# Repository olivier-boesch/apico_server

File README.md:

# apico_server

Code pour ruches connectées

Projet du lycée Saint Exupéry

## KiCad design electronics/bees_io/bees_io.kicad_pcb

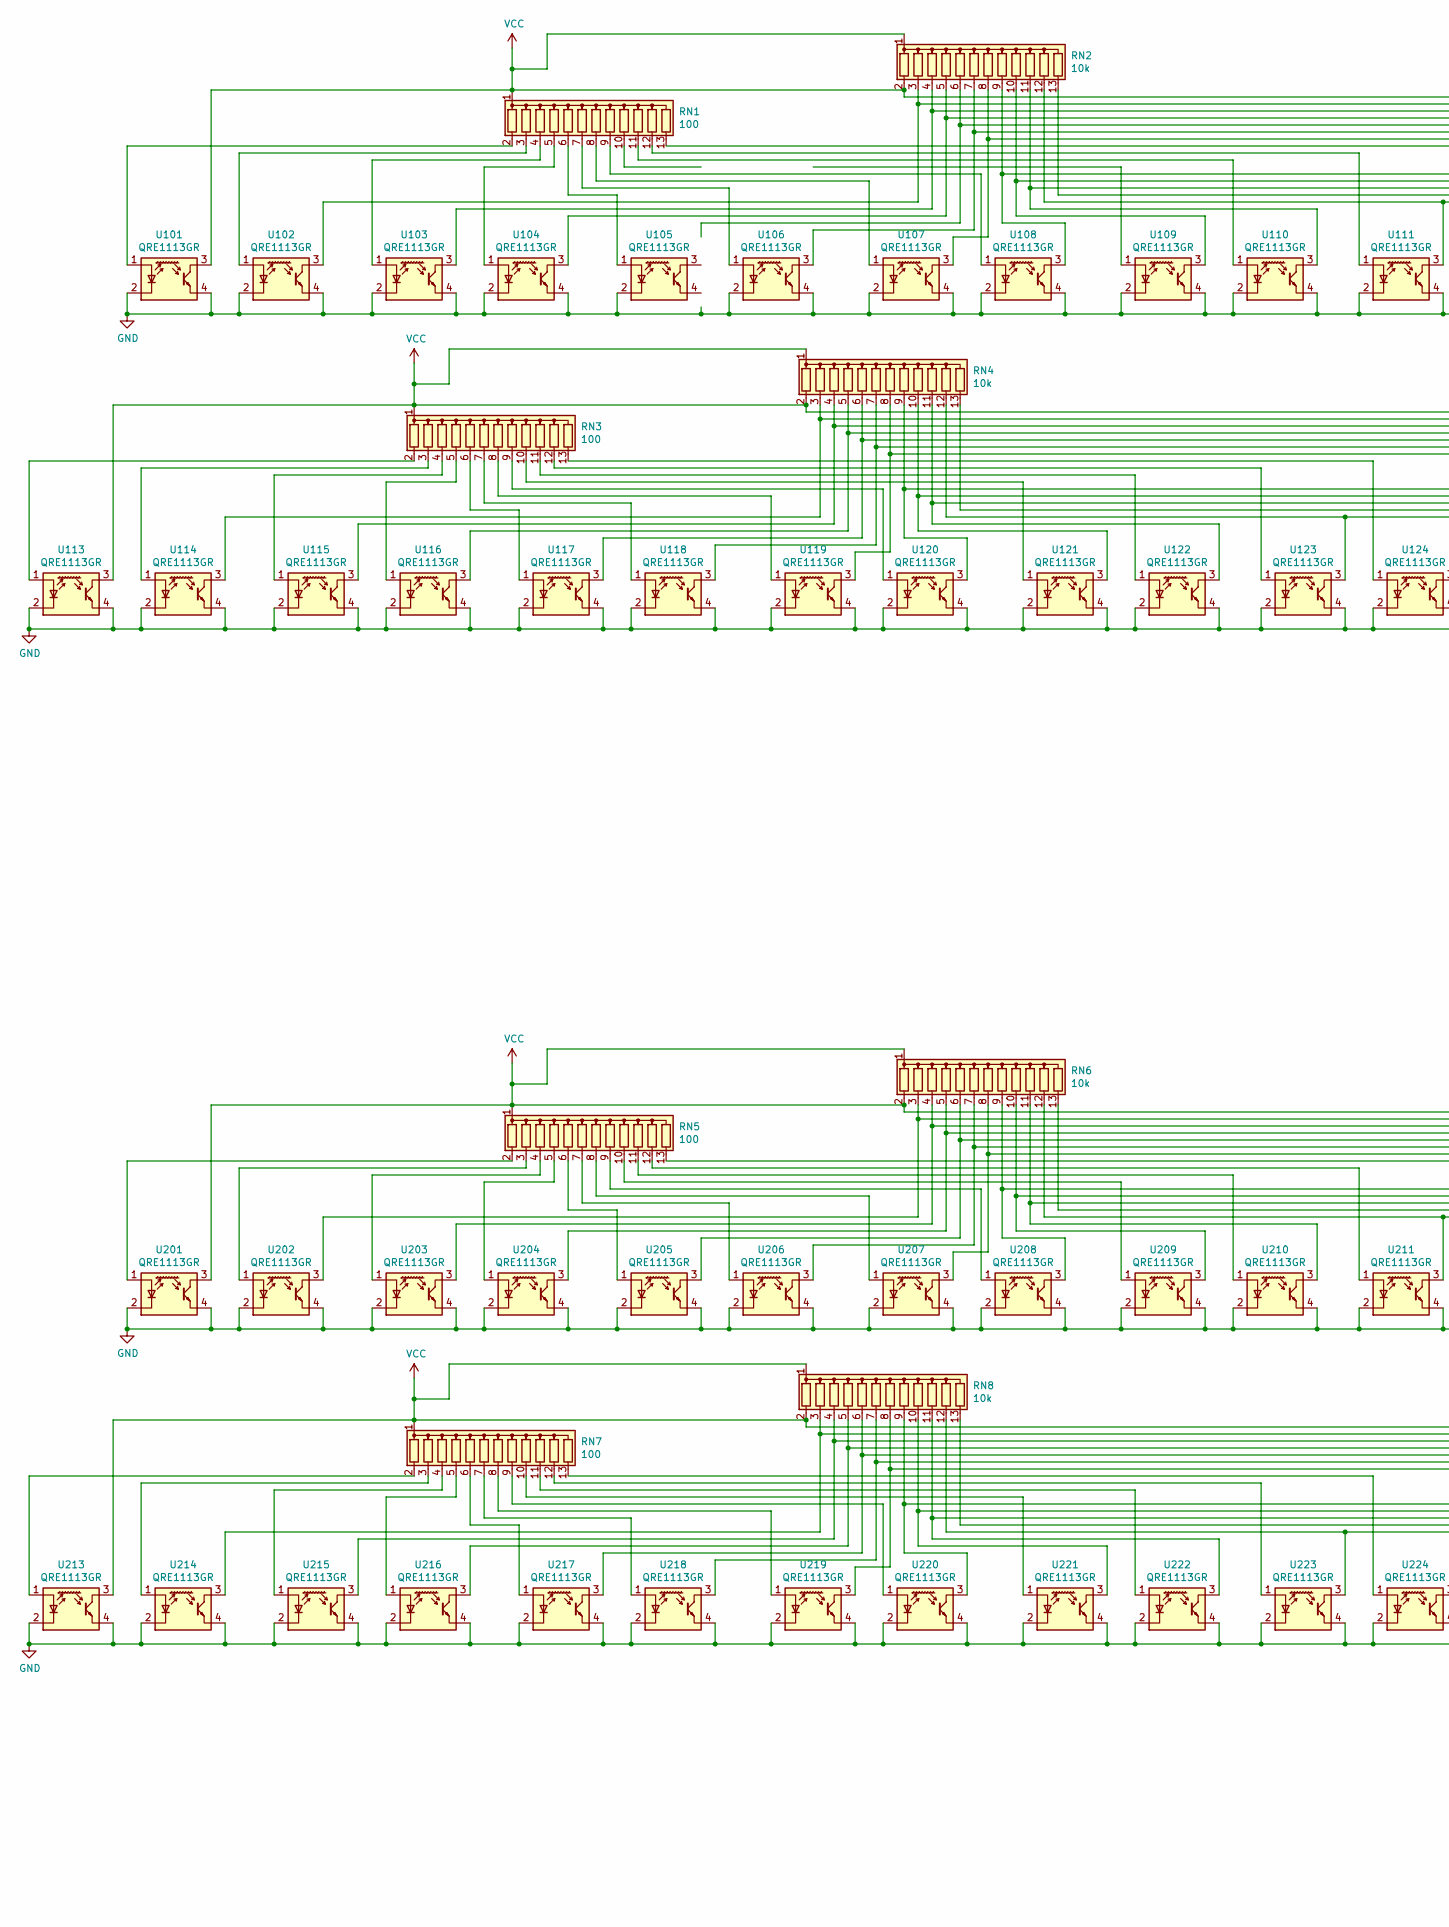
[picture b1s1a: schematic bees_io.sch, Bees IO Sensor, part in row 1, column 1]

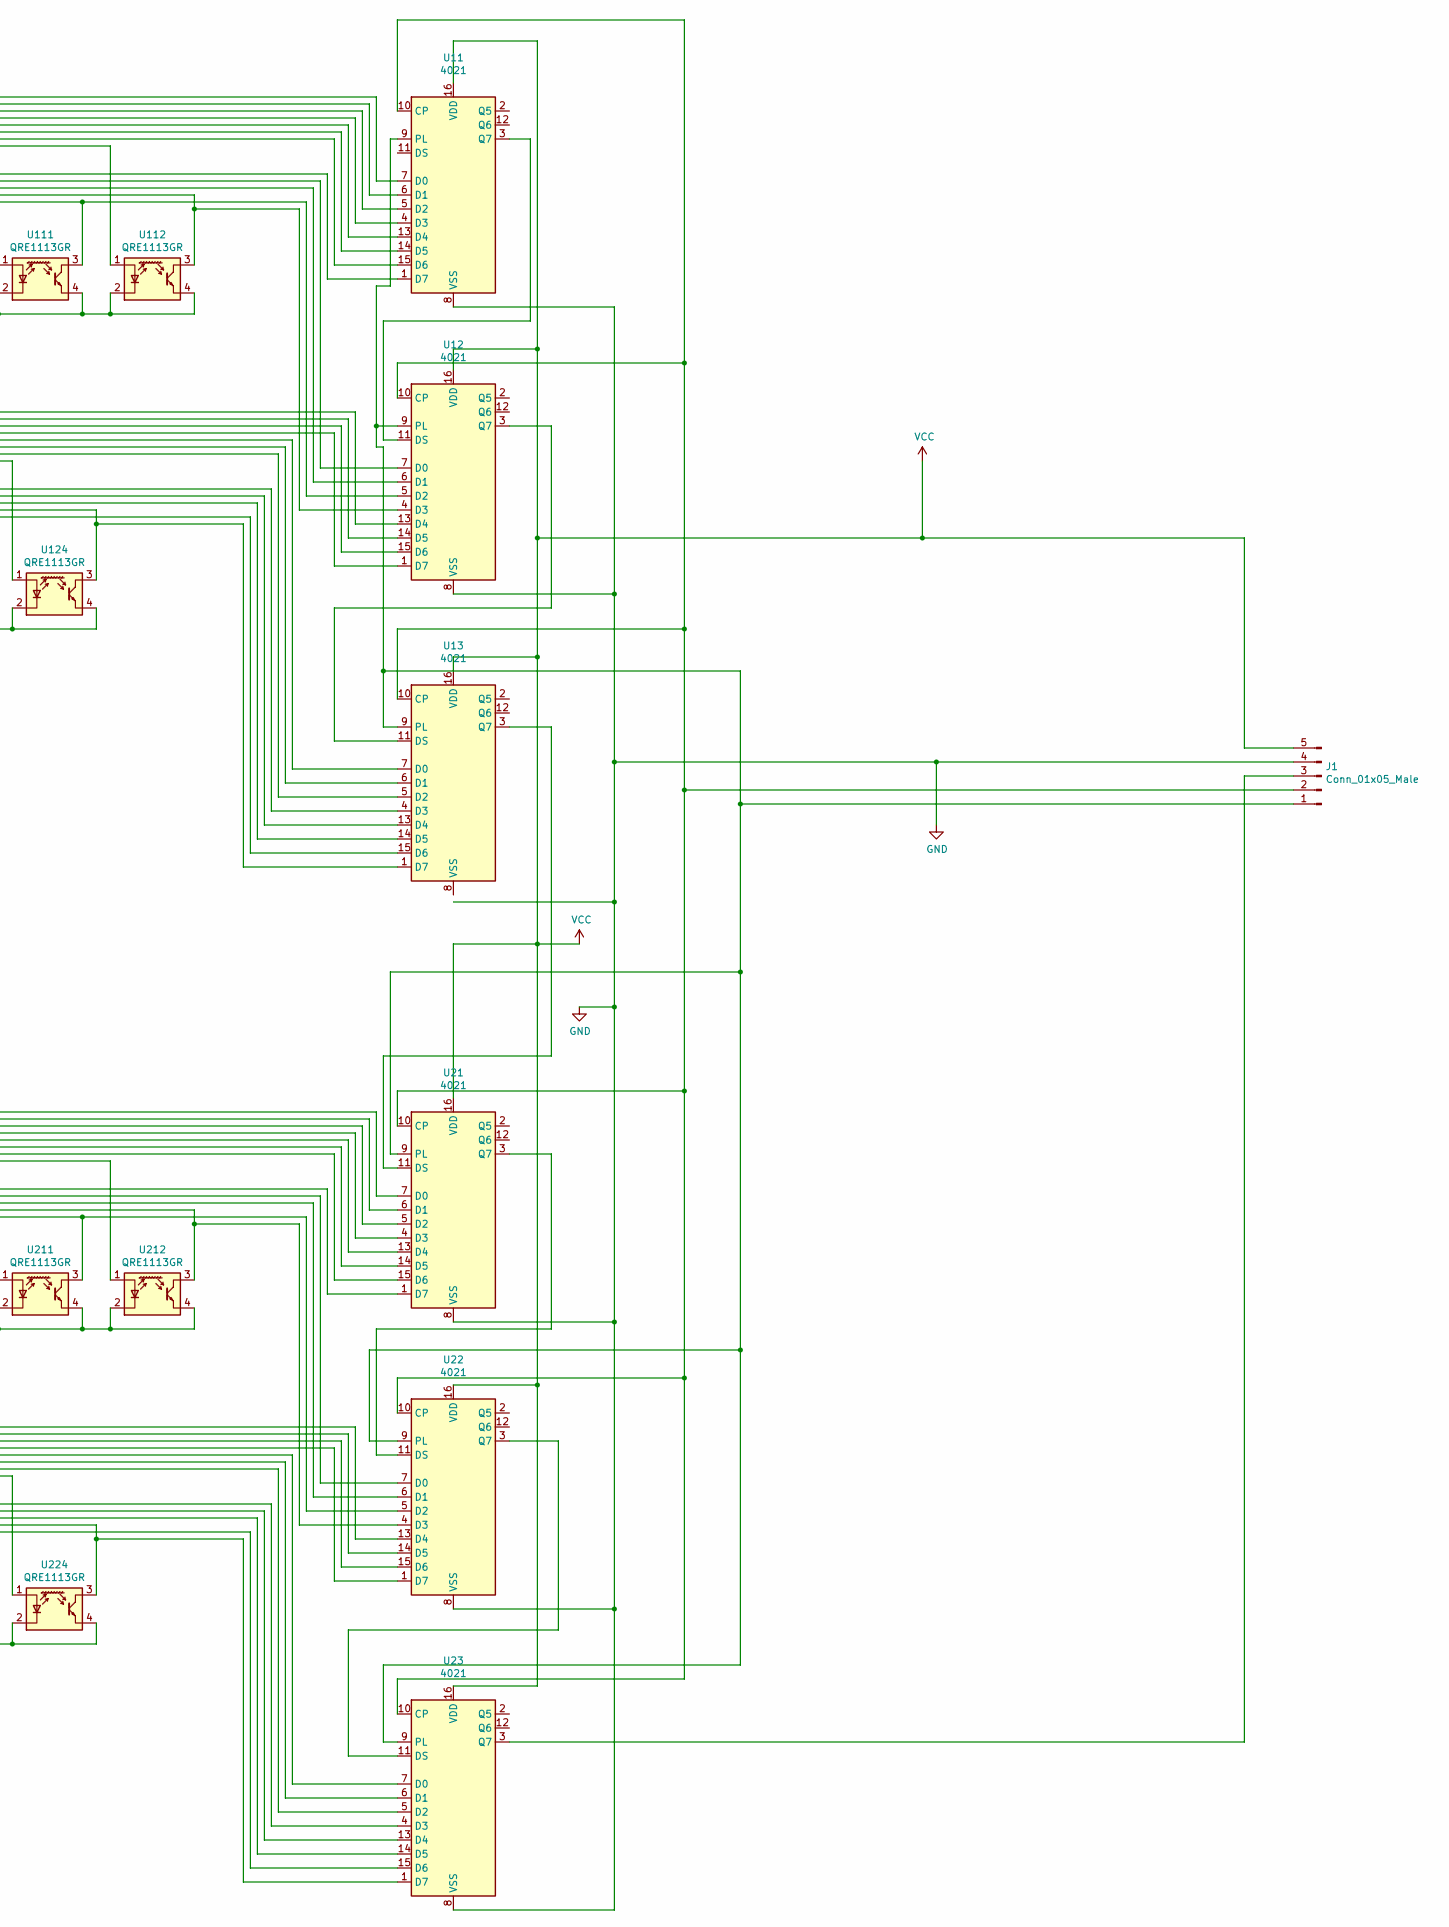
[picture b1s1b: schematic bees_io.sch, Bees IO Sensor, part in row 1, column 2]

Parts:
J1: Conn_01x05_Male; TerminalBlock_bornier-5_P5.08mm
RN1, RN3, RN5, RN7: 100; R_Cat16-8
RN2, RN4, RN6, RN8: 10k; R_Cat16-8
U11, U12, U13, U21, U22, U23: 4021; SO-16_5.3x10.2mm_P1.27mm
U101, U102, U103, U104, U105, U106, U107, U108, U109, U110, U111, U112, U113, U114, U115, U116, U117, U118, U119, U120, U121, U122, U123, U124, U201, U202, U203, U204, U205, U206, U207, U208, U209, U210, U211, U212, U213, U214, U215, U216, U217, U218, U219, U220, U221, U222, U223, U224: QRE1113GR; OnSemi_CASE100CY

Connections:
GND: J1.4, U11.8 (VSS), U12.8 (VSS), U21.8 (VSS), U22.8 (VSS), U23.8 (VSS), U101.2 (K), U101.4, U102.2 (K), U102.4, U103.2 (K), U103.4, U104.2 (K), U104.4, U105.2 (K), U106.2 (K), U106.4, U107.2 (K), U107.4, U108.2 (K), U108.4, U109.2 (K), U109.4, U110.2 (K), U110.4, U111.2 (K), U111.4, U112.2 (K), U112.4, U113.2 (K), U113.4, U114.2 (K), U114.4, U115.2 (K), U115.4, U116.2 (K), U116.4, U117.2 (K), U117.4, U118.2 (K), U118.4, U119.2 (K), U119.4, U120.2 (K), U120.4, U121.2 (K), U121.4, U122.2 (K), U122.4, U123.2 (K), U123.4, U124.2 (K), U124.4, U201.2 (K), U201.4, U202.2 (K), U202.4, U203.2 (K), U203.4, U204.2 (K), U204.4, U205.2 (K), U205.4, U206.2 (K), U206.4, U207.2 (K), U207.4, U208.2 (K), U208.4, U209.2 (K), U209.4, U210.2 (K), U210.4, U211.2 (K), U211.4, U212.2 (K), U212.4, U213.2 (K), U213.4, U214.2 (K), U214.4, U215.2 (K), U215.4, U216.2 (K), U216.4, U217.2 (K), U217.4, U218.2 (K), U218.4, U219.2 (K), U219.4, U220.2 (K), U220.4, U221.2 (K), U221.4, U222.2 (K), U222.4, U223.2 (K), U223.4, U224.2 (K), U224.4
unnamed: J1.1, U11.9 (PL), U12.9 (PL), U13.9 (PL), U21.9 (PL), U22.9 (PL), U23.9 (PL)
unnamed: J1.2, U11.10 (CP), U12.10 (CP), U13.10 (CP), U21.10 (CP), U22.10 (CP), U23.10 (CP)
unnamed: J1.3, U23.3 (Q7)
unnamed: RN1.2 (R1), U101.1 (A)
unnamed: RN1.3 (R2), U102.1 (A)
unnamed: RN1.4 (R3), U103.1 (A)
unnamed: RN1.5 (R4), U104.1 (A)
unnamed: RN1.6 (R5), U105.1 (A)
unnamed: RN1.7 (R6), U106.1 (A)
unnamed: RN1.8 (R7), U107.1 (A)
unnamed: RN1.9 (R8), U108.1 (A)
unnamed: RN1.11 (R10), U110.1 (A)
unnamed: RN1.12 (R11), U111.1 (A)
unnamed: RN1.13 (R12), U112.1 (A)
unnamed: RN2.3 (R2), U11.6 (D1), U102.3
unnamed: RN2.4 (R3), U11.5 (D2), U103.3
unnamed: RN2.5 (R4), U11.4 (D3), U104.3
unnamed: RN2.6 (R5), U11.13 (D4)
unnamed: RN2.7 (R6), U11.14 (D5), U106.3
unnamed: RN2.8 (R7), U11.15 (D6), U107.3
unnamed: RN2.9 (R8), U11.1 (D7), U108.3
unnamed: RN2.10 (R9), U12.7 (D0), U109.3
unnamed: RN2.11 (R10), U12.6 (D1), U110.3
unnamed: RN2.12 (R11), U12.5 (D2), U111.3
unnamed: RN2.13 (R12), U12.4 (D3), U112.3
unnamed: RN3.2 (R1), U113.1 (A)
unnamed: RN3.3 (R2), U114.1 (A)
unnamed: RN3.4 (R3), U115.1 (A)
unnamed: RN3.5 (R4), U116.1 (A)
unnamed: RN3.6 (R5), U117.1 (A)
unnamed: RN3.7 (R6), U118.1 (A)
unnamed: RN3.8 (R7), U119.1 (A)
unnamed: RN3.9 (R8), U120.1 (A)
unnamed: RN3.10 (R9), U121.1 (A)
unnamed: RN3.11 (R10), U122.1 (A)
unnamed: RN3.12 (R11), U123.1 (A)
unnamed: RN3.13 (R12), U124.1 (A)
unnamed: RN4.3 (R2), U12.14 (D5), U114.3
unnamed: RN4.4 (R3), U12.15 (D6), U115.3
unnamed: RN4.5 (R4), U12.1 (D7), U116.3
unnamed: RN4.6 (R5), U13.7 (D0), U117.3
unnamed: RN4.7 (R6), U13.6 (D1), U118.3
unnamed: RN4.8 (R7), U13.5 (D2), U119.3
unnamed: RN4.9 (R8), U13.4 (D3), U120.3
unnamed: RN4.10 (R9), U13.13 (D4), U121.3
unnamed: RN4.11 (R10), U13.14 (D5), U122.3
unnamed: RN4.12 (R11), U13.15 (D6), U123.3
unnamed: RN4.13 (R12), U13.1 (D7), U124.3
unnamed: RN5.2 (R1), U201.1 (A)
unnamed: RN5.3 (R2), U202.1 (A)
unnamed: RN5.4 (R3), U203.1 (A)
unnamed: RN5.5 (R4), U204.1 (A)
unnamed: RN5.6 (R5), U205.1 (A)
unnamed: RN5.7 (R6), U206.1 (A)
unnamed: RN5.8 (R7), U207.1 (A)
unnamed: RN5.9 (R8), U208.1 (A)
unnamed: RN5.10 (R9), U209.1 (A)
unnamed: RN5.11 (R10), U210.1 (A)
unnamed: RN5.12 (R11), U211.1 (A)
unnamed: RN5.13 (R12), U212.1 (A)
unnamed: RN6.3 (R2), U21.6 (D1), U202.3
unnamed: RN6.4 (R3), U21.5 (D2), U203.3
unnamed: RN6.5 (R4), U21.4 (D3), U204.3
unnamed: RN6.6 (R5), U21.13 (D4), U205.3
unnamed: RN6.7 (R6), U21.14 (D5), U206.3
unnamed: RN6.8 (R7), U21.15 (D6), U207.3
unnamed: RN6.9 (R8), U21.1 (D7), U208.3
unnamed: RN6.10 (R9), U22.7 (D0), U209.3
unnamed: RN6.11 (R10), U22.6 (D1), U210.3
unnamed: RN6.12 (R11), U22.5 (D2), U211.3
unnamed: RN6.13 (R12), U22.4 (D3), U212.3
unnamed: RN7.2 (R1), U213.1 (A)
unnamed: RN7.3 (R2), U214.1 (A)
unnamed: RN7.4 (R3), U215.1 (A)
unnamed: RN7.5 (R4), U216.1 (A)
unnamed: RN7.6 (R5), U217.1 (A)
unnamed: RN7.7 (R6), U218.1 (A)
unnamed: RN7.8 (R7), U219.1 (A)
unnamed: RN7.9 (R8), U220.1 (A)
unnamed: RN7.10 (R9), U221.1 (A)
unnamed: RN7.11 (R10), U222.1 (A)
unnamed: RN7.12 (R11), U223.1 (A)
unnamed: RN7.13 (R12), U224.1 (A)
unnamed: RN8.3 (R2), U22.14 (D5), U214.3
unnamed: RN8.4 (R3), U22.15 (D6), U215.3
unnamed: RN8.5 (R4), U22.1 (D7), U216.3
unnamed: RN8.6 (R5), U23.7 (D0), U217.3
unnamed: RN8.7 (R6), U23.6 (D1), U218.3
unnamed: RN8.8 (R7), U23.5 (D2), U219.3
unnamed: RN8.9 (R8), U23.4 (D3), U220.3
unnamed: RN8.10 (R9), U23.13 (D4), U221.3
unnamed: RN8.11 (R10), U23.14 (D5), U222.3
unnamed: RN8.12 (R11), U23.15 (D6), U223.3
unnamed: RN8.13 (R12), U23.1 (D7), U224.3
unnamed: U11.3 (Q7), U12.11 (DS)
unnamed: U12.3 (Q7), U13.11 (DS)
unnamed: U13.3 (Q7), U21.11 (DS)
unnamed: U21.3 (Q7), U22.11 (DS)
unnamed: U22.3 (Q7), U23.11 (DS)
VCC: J1.5, RN1.1 (common), RN2.1 (common), RN2.2 (R1), RN3.1 (common), RN4.1 (common), RN4.2 (R1), RN5.1 (common), RN6.1 (common), RN6.2 (R1), RN7.1 (common), RN8.1 (common), RN8.2 (R1), U11.7 (D0), U11.16 (VDD), U12.13 (D4), U12.16 (VDD), U13.16 (VDD), U21.7 (D0), U21.16 (VDD), U22.13 (D4), U22.16 (VDD), U23.16 (VDD), U101.3, U113.3, U201.3, U213.3

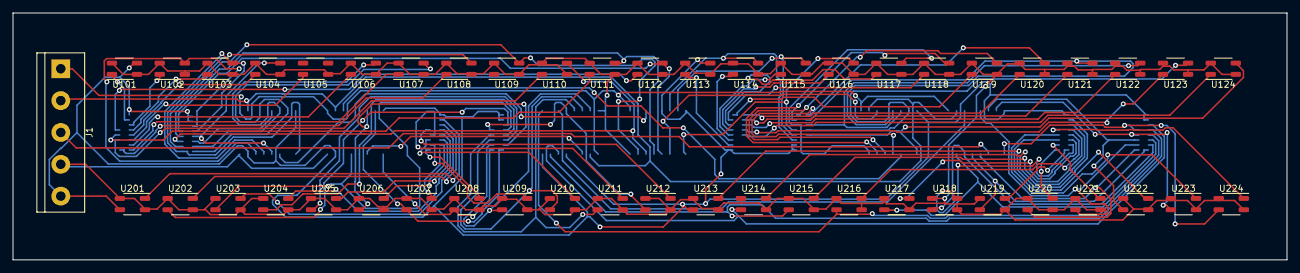
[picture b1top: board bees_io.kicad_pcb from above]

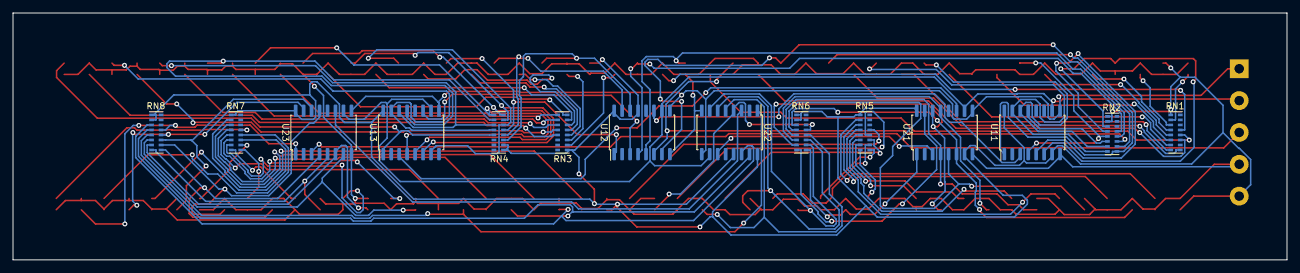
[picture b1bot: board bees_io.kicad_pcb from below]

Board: 2 copper layers, 203.2 x 39.4 mm, 63 parts (14 on the bottom side), 101 nets.

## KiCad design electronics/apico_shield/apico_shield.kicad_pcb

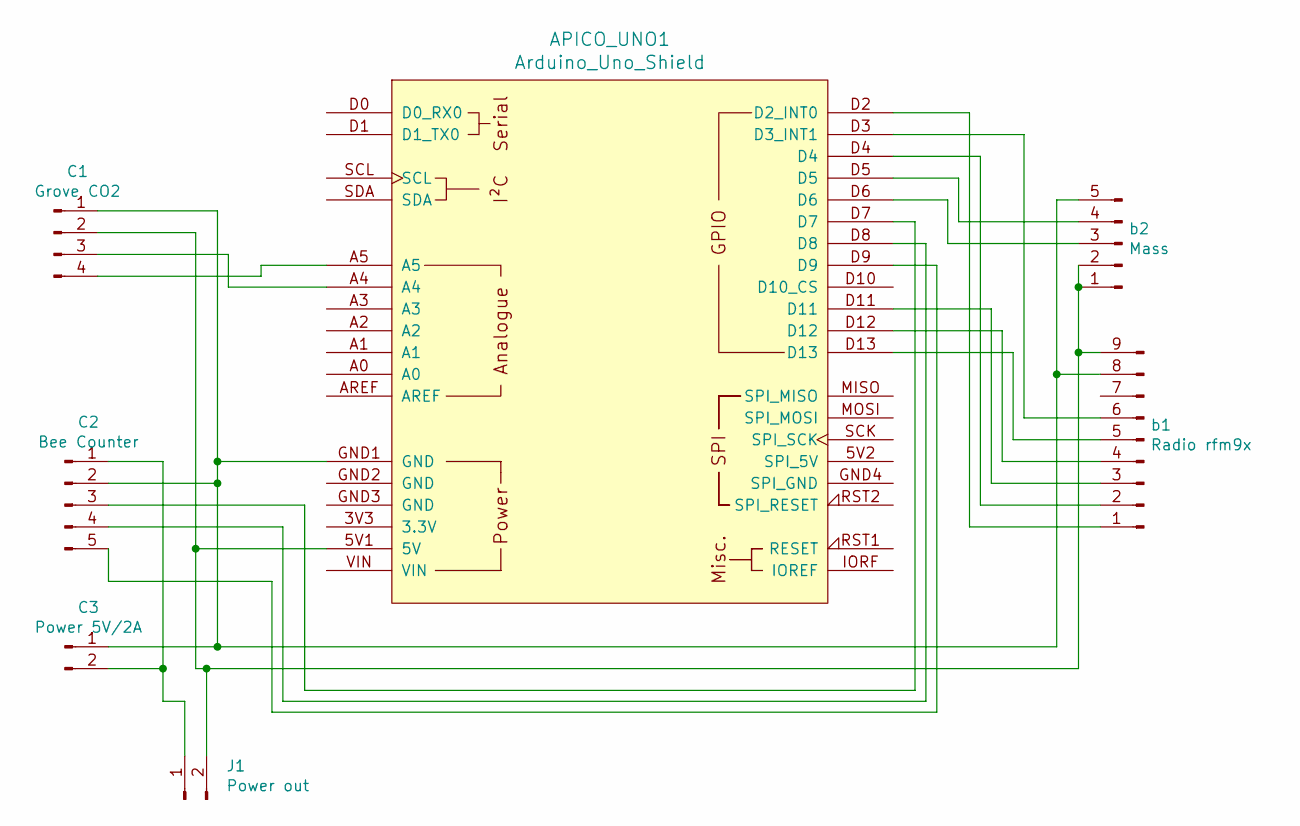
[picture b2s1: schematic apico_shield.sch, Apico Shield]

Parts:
APICO_UNO1: Arduino_Uno_Shield
C1: Grove CO2; NS-Tech_Grove_1x04_P2mm_Vertical
C2: Bee Counter; TerminalBlock_bornier-5_P5.08mm
C3: Power 5V/2A; TerminalBlock_bornier-2_P5.08mm
J1: Power out; PinHeader_1x02_P2.54mm_Vertical
b1: Radio rfm9x; PinHeader_1x09_P2.54mm_Vertical
b2: Mass; PinHeader_1x05_P2.54mm_Vertical

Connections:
unnamed: APICO_UNO1.5V1 (5V), C1.2, J1.2, b1.9, b2.1, b2.2
unnamed: APICO_UNO1.A4, C1.3
unnamed: APICO_UNO1.A5, C1.4
unnamed: APICO_UNO1.D2 (D2_INT0), b1.1
unnamed: APICO_UNO1.D3 (D3_INT1), b1.6
unnamed: APICO_UNO1.D4, b1.2
unnamed: APICO_UNO1.D5, b2.4
unnamed: APICO_UNO1.D6, b2.3
unnamed: APICO_UNO1.D7, C2.3
unnamed: APICO_UNO1.D8, C2.4
unnamed: APICO_UNO1.D9, C2.5
unnamed: APICO_UNO1.D11, b1.3
unnamed: APICO_UNO1.D12, b1.4
unnamed: APICO_UNO1.D13, b1.5
unnamed: APICO_UNO1.GND1 (GND), C1.1, C2.2, C3.1, b1.8, b2.5
unnamed: C2.1, C3.2, J1.1

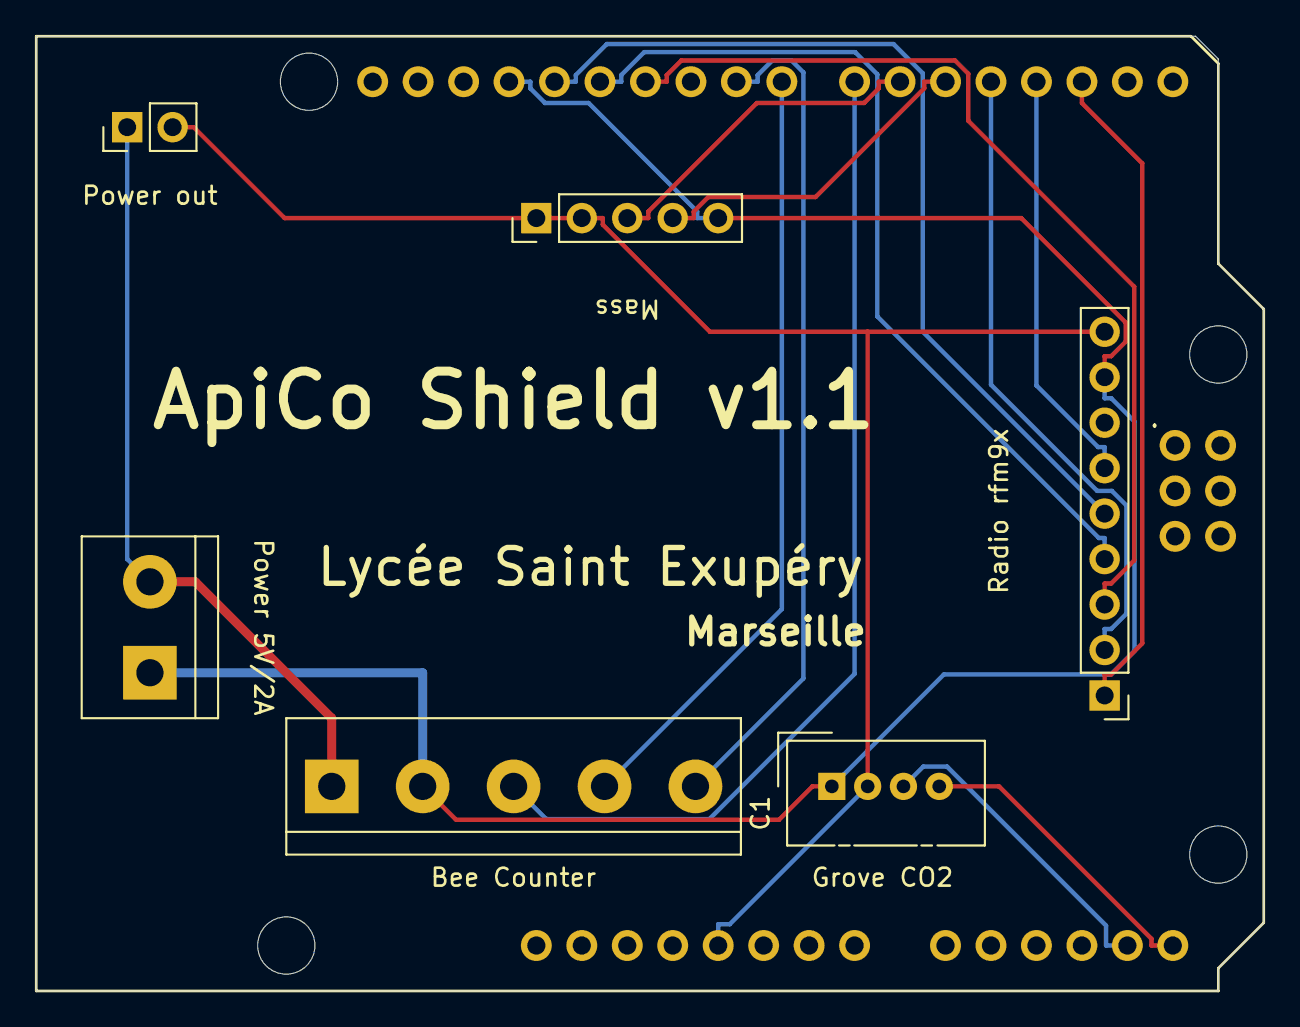
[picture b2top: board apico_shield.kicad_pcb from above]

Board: 2 copper layers, 68.6 x 53.3 mm, 7 parts (0 on the bottom side), 16 nets.

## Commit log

2021-11-06 updated pcb
2021-11-06 removed unused code
2021-11-07 added 3d files
2021-11-07 minor changes
2021-11-12 code rework
2021-11-12 added lora logo
2021-11-12 modified electronics

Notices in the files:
electronics/apico_shield/apico_shield.kicad_pcb:
Olivier Boesch (c) 2021
